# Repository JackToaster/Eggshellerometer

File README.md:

# Eggshellerometer

An acceleration-logging smart egg for egg drop experiments.

## Features
The goal of this project is to create a logging high-acceleration accelerometer. It can be used in place of an egg for egg-drop type experiments, and also as an open-source, hackable tool for recording high-acceleration events such as impacts or rocket launches. 
- 200G Accelerometer recording data at up to 3.2kHz (ADXL375)
- Built-in wifi/bluetooth with an ESP32-S3 microcontroller - allows connection to a phone/tablet companion app to visualize data
- tiny 0.5" OLED display to display information
- Tiny form factor - 30x50mm PCB which fits in a case the size of a large chicken egg
- Battery powered with a USB-C connector for charging/updating
- Configurable wakeup threshold to record acceleration events over a long period of time without draining battery
- Low cost, <$20 assembled in small quantities
- Open-source hardware and firmware (WIP)
- No chickens harmed in the making

## Status of the project
Currently, only the electrical hardware has been designed. I will include firmware, CAD & 3D printing files for enclosures, and any other information in this repository as I create them (Likely after I receive the first batch of prototypes).

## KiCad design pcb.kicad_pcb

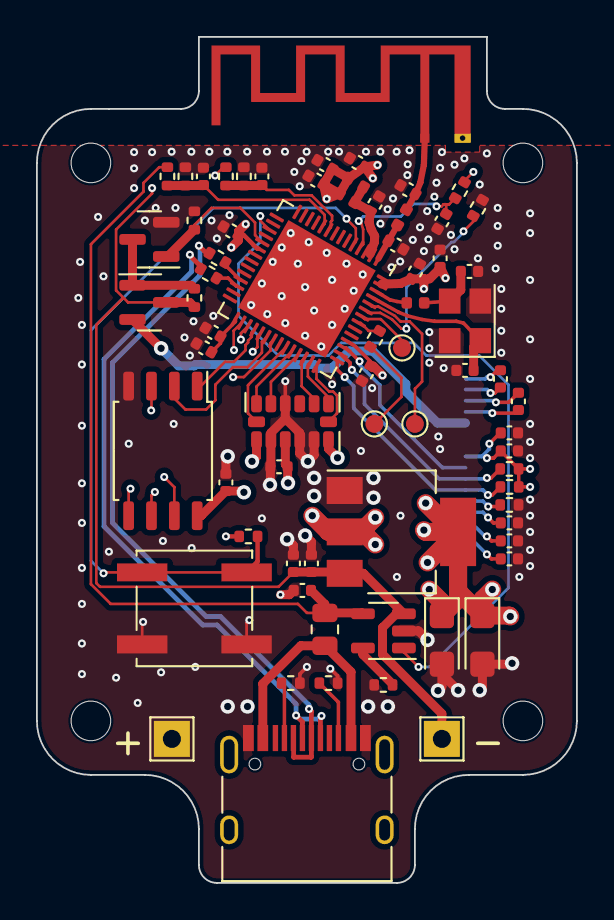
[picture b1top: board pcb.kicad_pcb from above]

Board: 4 copper layers, 30.0 x 47.0 mm, 75 parts (1 on the bottom side), 54 nets.

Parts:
AE2: PCB Antenna; Texas_SWRA117D_2.4GHz_Left
C7, C28, C30: 10u; C_0402_1005Metric
C8, C20: 10u tantalum; CP_EIA-3216-10_Kemet-I
C9, C10, C13, C18, C22, C23, C24, C26, C29, C32, C38, C39: 100n; C_0402_1005Metric
C11, C12, C16: 4u7; C_0402_1005Metric
C14, C17, C25, C27, C31, C33: 1u; C_0402_1005Metric
C15: 2u2; C_0402_1005Metric
C34, C35: 22p; C_0402_1005Metric
C36: 4p7; C_0402_1005Metric
C37: 3p3; C_0402_1005Metric
FB1: 100R@100MHz; R_0805_2012Metric
H1, H2, H3, H4: MountingHole; MountingHole_2.2mm_M2
J1: USB_C_Receptacle_USB2.0; USB_C_Receptacle_HRO_TYPE-C-31-M-12
J2: OLED; FPC_14
L1, L2: 3.9nH; L_0402_1005Metric
L3: 15nH; L_0402_1005Metric
L4: 1.8nH; L_0402_1005Metric
Q3: 2N7002; SOT-23
Q4: Si2301CDS; SOT-23
R1, R3, R5, R8, R10, R11, R13, R14: 10k; R_0402_1005Metric
R6, R7: 5k1; R_0402_1005Metric
R9: 560k; R_0402_1005Metric
R15, R16, R17, R18: 120k; R_0402_1005Metric
R20: 470; R_0402_1005Metric
R21, R22: 0R; R_0402_1005Metric
SW1: SW_Push; SW_Push_1P1T_NO_CK_KSC7xxJ
TP1: Batt+; TestPoint_THTPad_2.0x2.0mm_Drill1.0mm
TP2: Batt-; TestPoint_THTPad_2.0x2.0mm_Drill1.0mm
TP3: TXD; TestPoint_Pad_D1.0mm
TP4: RXD; TestPoint_Pad_D1.0mm
TP5: BOOT1; TestPoint_Pad_D1.0mm
U1: ADXL375; LGA-14_3x5mm_P0.8mm_LayoutBorder1x6y
U3: AMS1117-3.3; SOT-223-3_TabPin2
U4: MCP73831-2-OT; SOT-23-5
U5: W25Q128JVS; SOIC-8_5.23x5.23mm_P1.27mm
U6: ESP32-S3; QFN-56-1EP_7x7mm_P0.4mm_EP5.6x5.6mm
Y1: 40MHz 15pF; Crystal_SMD_3225-4Pin_3.2x2.5mm

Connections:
+3.3V: C8.1, C10.1, C12.1, C13.1, C20.1, C22.1, C23.1, C26.1, C27.1, C28.1, C30.1, C31.1, C32.1, J2.8, L1.1, L2.1, R1.1, R10.1, R11.1, R14.1, U1.1 (Vdd_I/O), U1.3 (RES), U1.6 (Vs), U3.2 (VO), U5.8 (VCC), U6.20 (VDD3P3_RTC), U6.46 (VDD3P3_CPU), U6.55 (VDDA), U6.56 (VDDA)
/ANT_RF: AE2.1, C37.1, L4.1
/BOOT: R1.2, SW1.2, U6.5 (GPIO0/BOOT)
/ESP_RF: C36.1, L4.2, U6.1 (LNA_IN/RF)
/OLED/C1N: C14.2, J2.4
/OLED/C1P: C14.1, J2.3
/OLED/C2N: C17.2, J2.2
/OLED/C2P: C17.1, J2.1
/OLED/IREF: J2.12, R9.1
/OLED/OLED-VBAT: J2.5, Q4.2 (S)
/OLED/VCC: C16.1, C18.1, J2.14
/OLED/VCOMH: C15.1, J2.13
/VDD_SPI: C24.1, C25.1, U6.29 (VDD_SPI)
ACCEL-INT1: U1.8 (INT1), U6.41 (GPIO36)
ACCEL-INT2: U1.9 (INT2), U6.40 (GPIO35)
ACCEL-SCK: U1.14 (SCL/SCLK), U6.37 (SPICLK_P/GPIO47)
ACCEL-SDI: U1.13 (SDA/SDI/SDIO), U6.38 (GPIO33)
ACCEL-SDO: U1.12 (SDO/ADDR), U6.39 (GPIO34)
ACCEL-nCS: U1.7 (~CS), U6.42 (GPIO37)
CHARGE_STAT: U4.1 (STAT), U6.17 (GPIO12/ADC2_CH1)
FLASH-CLK: U5.6 (CLK), U6.33 (SPICLK/GPIO30)
FLASH-D: U5.5 (DI(IO0)), U6.35 (SPID/GPIO32)
FLASH-HD: U5.7 (IO3), U6.30 (SPIHD/GPIO27)
FLASH-Q: U5.2 (DO(IO1)), U6.34 (SPIQ/GPIO31)
FLASH-WP: U5.3 (IO2), U6.31 (SPIWP/GPIO28)
FLASH-nCS: U5.1 (~CS), U6.32 (SPICS0/GPIO29)
GND: AE2.2, C7.2, C8.2, C9.2, C10.2, C11.2, C12.2, C13.2, C15.2, C16.2, C18.2, C20.2, C22.2, C23.2, C24.2, C25.2, C26.2, C27.2, C28.2, C29.2, C30.2, C31.2, C32.2, C33.2, C34.1, C35.2, C36.2, C37.2, C38.2, C39.2, J1.A1 (GND), J1.A12 (GND), J1.B1 (GND), J1.B12 (GND), J2.7, Q3.2 (S), R3.2, R5.2, R6.2, R7.1, R9.2, R13.2, R16.2, R18.2, SW1.1, TP2.1, U1.2 (GND), U1.4 (GND), U1.5 (GND), U1.11 (RES), U3.1 (GND), U4.2 (V_{SS}), U5.4 (GND), U6.57 (GND), Y1.2, Y1.4
I2C_SCL: J2.10, R11.2, U6.44 (MTCK/JTAG/GPIO39)
I2C_SDA: J2.11, R10.2, U6.43 (GPIO38)
unnamed: C34.2, L3.1, Y1.3
unnamed: FB1.1, J1.A4 (VBUS), J1.A9 (VBUS), J1.B4 (VBUS), J1.B9 (VBUS)
unnamed: J1.A5 (CC1), R6.1
unnamed: J1.B5 (CC2), R7.2
unnamed: Q3.3 (D), Q4.1 (G), R8.2
unnamed: R20.2, TP3.1
unnamed: R5.1, U4.5 (PROG)
unnamed: C33.1, R14.2, U6.4 (CHIP_PU/RESET)
unnamed: R22.1, U6.25 (GPIO19/USB_D-/ADC2_CH8)
unnamed: R21.1, U6.26 (GPIO20/USB_D+/ADC2_CH9)
unnamed: R13.1, U6.51 (GPIO45)
unnamed: TP5.1, U6.52 (GPIO46)
unnamed: TP4.1, U6.50 (U0RXD/PROG/GPIO44)
unnamed: R20.1, U6.49 (U0TXD/PROG/GPIO43)
unnamed: C35.1, U6.53 (XTAL_N), Y1.1
unnamed: L3.2, U6.54 (XTAL_P)
OLED_ENABLE: Q3.1 (G), R3.1, U6.19 (GPIO14/ADC2_CH3)
OLED_RESET: J2.9, U6.45 (MTDO/JTAG/GPIO40)
USB_D+: J1.A6 (D+), J1.B6 (D+), R21.2
USB_D-: J1.A7 (D-), J1.B7 (D-), R22.2
USB_VBUS: C11.1, FB1.2, R17.1, U4.4 (V_{DD})
VBAT: C7.1, C9.1, Q4.3 (D), R8.1, R15.1, TP1.1, U3.3 (VI), U4.3 (V_{BAT})
VBAT_MEAS: C39.1, R15.2, R16.1, U6.9 (GPIO4/ADC1_CH3)
VBUS_MEAS: C38.1, R17.2, R18.1, U6.10 (GPIO5/ADC1_CH4)
VDD3P3: C29.1, L1.2, L2.2, U6.2 (VDD3P3), U6.3 (VDD3P3)

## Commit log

2023-07-02 inital layout
2023-07-03 Added silkscreen art and fixed overlapping things
2023-07-03 fixed library issues
2023-07-03 add submodules to CI/CD
2023-07-03 fix yaml syntax
2023-07-04 added part numbers
2023-07-09 Bare ESP layout
2023-07-09 fix erc/drc
2023-07-09 fix overlap
2023-07-09 fixed layout
2023-07-12 Use bare ESP32 chip instead of module (#1)
    * fixed library issues
    * add submodules to CI/CD
    * fix yaml syntax
    * added part numbers
    * Bare ESP layout
    * fix erc/drc
2023-07-15 Incorporate feedback from cnlohr
